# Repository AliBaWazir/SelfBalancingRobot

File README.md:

# README #

This README would normally document whatever steps are necessary to get your application up and running.

### What is this repository for? ###

This is Team Foxtrot's Repo for Self-Balancing Robot (SBR)

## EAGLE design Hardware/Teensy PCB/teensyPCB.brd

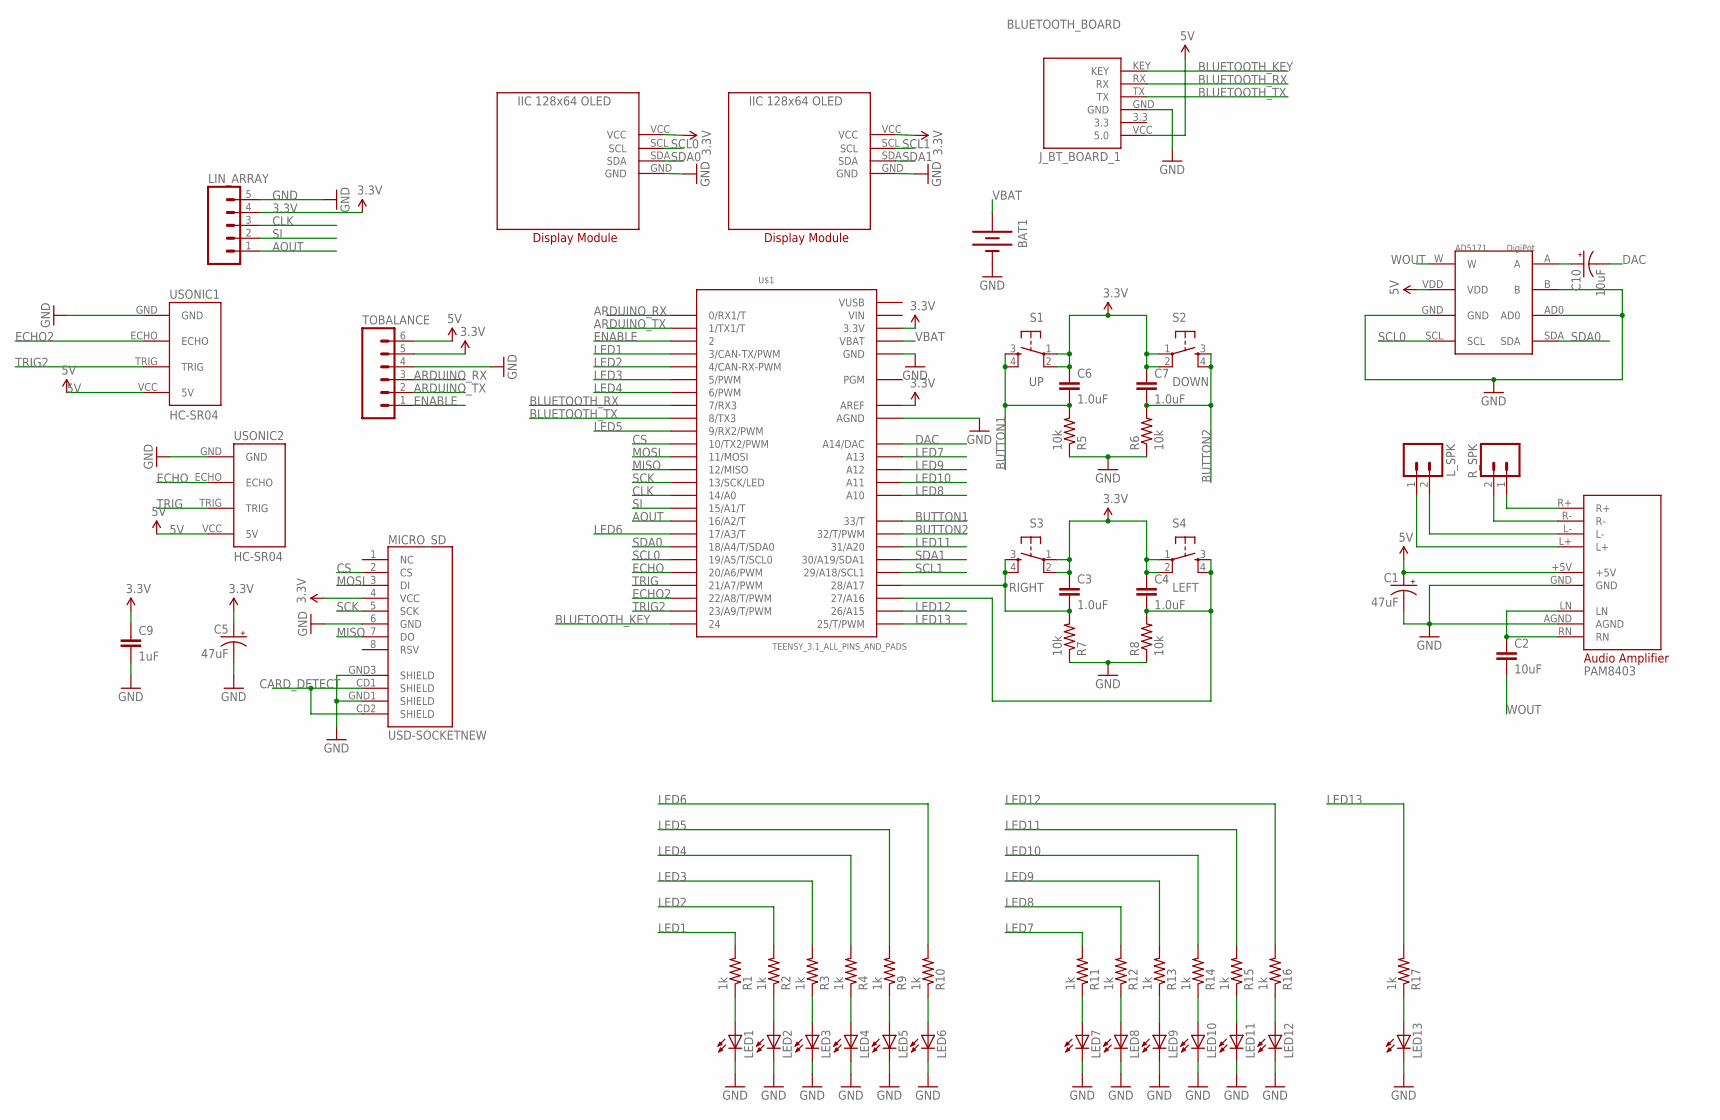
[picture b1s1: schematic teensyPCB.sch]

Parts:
BAT1: BATTERY20PTH; BATTCOM_20MM_PTH
C1, C5: 47uF; EIA3528
C2: 10uF; 0805
C3, C4, C6, C7: 1.0uF; 0805
C9: 1uF; 0805
C10: 10uF; EIA3528
J_BT_BOARD_1: BLUETOOTH_BOARD; BT_BOARD_FOOTPRINT
LED1, LED2, LED3, LED4, LED5, LED6, LED7, LED8, LED9, LED10, LED11, LED12, LED13: LEDCHIP-LED0805; CHIP-LED0805
LIN_ARRAY: M05LOCK; 1X05_LOCK
L_SPK: M02PTH; 1X02
MICRO_SD: USD-SOCKETNEW; MICRO-SD-SOCKET-PP
R1, R2, R3, R4, R9, R10, R11, R12, R13, R14, R15, R16, R17: 1k; 0805
R5, R6, R7, R8: 10k; 0805
R_SPK: M02PTH; 1X02
S1: UP; TACTILE-SWITCH-SMD
S2: DOWN; TACTILE-SWITCH-SMD
S3: RIGHT; TACTILE-SWITCH-SMD
S4: LEFT; TACTILE-SWITCH-SMD
TOBALANCE: M06POLAR_LOCK; MOLEX-1X6_LOCK
U$1: TEENSY_3.1_ALL_PINS_AND_PADS; TEENSY3_ALL_PINS_&_PADS
U$2, U$3: IIC128X64OLED
U$4: AUDIOAMPEBAY_VERSION; AUDIOAMP
U$5: DIGIPOT; SOT23-8L
USONIC1, USONIC2: HC-SR04; HC-SR04_FOOTPRINT

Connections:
3.3V: C3.1, C4.1, C5.A (+), C6.1, C7.1, C9.1, LIN_ARRAY.4, MICRO_SD.4 (VCC), S1.1, S1.2, S2.1, S2.2, S3.1, S3.2, S4.1, S4.2, TOBALANCE.5, U$1.3.3V, U$1.3.3V1 (3.3V), U$1.3.3V2 (3.3V), U$1.AREF, U$2.VCC, U$3.VCC
5V: C1.A (+), J_BT_BOARD_1.VCC (5.0), TOBALANCE.6, U$4.+5V, U$5.VDD, USONIC1.VCC (5V), USONIC2.VCC (5V)
AOUT: LIN_ARRAY.1, U$1.16/A2 (16/A2/T)
ARDUINO_RX: TOBALANCE.3, U$1.0 (0/RX1/T)
ARDUINO_TX: TOBALANCE.2, U$1.1 (1/TX1/T)
BLUETOOTH_KEY: J_BT_BOARD_1.KEY, U$1.24
BLUETOOTH_RX: J_BT_BOARD_1.RX, U$1.7 (7/RX3)
BLUETOOTH_TX: J_BT_BOARD_1.TX, U$1.8 (8/TX3)
BUTTON1: C6.2, R5.2, S1.3, S1.4, U$1.33 (33/T)
BUTTON2: C7.2, R6.2, S2.3, S2.4, U$1.32 (32/T/PWM)
BUTTON3: C3.2, R7.2, S3.3, S3.4, U$1.28 (28/A17)
BUTTON4: C4.2, R8.2, S4.3, S4.4, U$1.27 (27/A16)
CARD_DETECT: MICRO_SD.CD1 (SHIELD), MICRO_SD.CD2 (SHIELD)
CLK: LIN_ARRAY.3, U$1.14/A0
CS: MICRO_SD.2 (CS), U$1.10 (10/TX2/PWM)
DAC: C10.C (-), U$1.RESET/DAC (A14/DAC)
ECHO: U$1.20/A6 (20/A6/PWM), USONIC2.ECHO
ECHO2: U$1.22/A8 (22/A8/T/PWM), USONIC1.ECHO
ENABLE: TOBALANCE.1, U$1.2
GND: BAT1.2 (-), C1.C (-), C5.C (-), C9.2, J_BT_BOARD_1.GND, LED1.C, LED2.C, LED3.C, LED4.C, LED5.C, LED6.C, LED7.C, LED8.C, LED9.C, LED10.C, LED11.C, LED12.C, LED13.C, LIN_ARRAY.5, MICRO_SD.6 (GND), MICRO_SD.GND1 (SHIELD), MICRO_SD.GND3 (SHIELD), R5.1, R6.1, R7.1, R8.1, TOBALANCE.4, U$1.AGND, U$1.GND, U$1.GND1 (GND), U$1.GND2 (GND), U$2.GND, U$3.GND, U$4.AGND, U$4.GND, U$5.AD0, U$5.B, U$5.GND, USONIC1.GND, USONIC2.GND
LED1: R1.2, U$1.3 (3/CAN-TX/PWM)
LED2: R2.2, U$1.4 (4/CAN-RX-PWM)
LED3: R3.2, U$1.5 (5/PWM)
LED4: R4.2, U$1.6 (6/PWM)
LED5: R9.2, U$1.9 (9/RX2/PWM)
LED6: R10.2, U$1.17/A3 (17/A3/T)
LED7: R11.2, U$1.A13
LED8: R12.2, U$1.A10
LED9: R13.2, U$1.A12
LED10: R14.2, U$1.A11
LED11: R15.2, U$1.31 (31/A20)
LED12: R16.2, U$1.26 (26/A15)
LED13: R17.2, U$1.25 (25/T/PWM)
MISO: MICRO_SD.7 (DO), U$1.12 (12/MISO)
MOSI: MICRO_SD.3 (DI), U$1.11 (11/MOSI)
unnamed: C2.1, U$4.LN, U$4.RN
unnamed: C10.A (+), U$5.A
unnamed: R_SPK.1, U$4.R+
unnamed: R_SPK.2, U$4.R-
unnamed: L_SPK.2, U$4.L-
unnamed: L_SPK.1, U$4.L+
unnamed: LED1.A, R1.1
unnamed: LED2.A, R2.1
unnamed: LED3.A, R3.1
unnamed: LED4.A, R4.1
unnamed: LED5.A, R9.1
unnamed: LED6.A, R10.1
unnamed: LED7.A, R11.1
unnamed: LED8.A, R12.1
unnamed: LED9.A, R13.1
unnamed: LED10.A, R14.1
unnamed: LED11.A, R15.1
unnamed: LED12.A, R16.1
unnamed: LED13.A, R17.1
SCK: MICRO_SD.5 (SCK), U$1.13 (13/SCK/LED)
SCL0: U$1.19/A5 (19/A5/T/SCL0), U$2.SCL, U$5.SCL
SCL1: U$1.29 (29/A18/SCL1), U$3.SCL
SDA0: U$1.18/A4 (18/A4/T/SDA0), U$2.SDA, U$5.SDA
SDA1: U$1.30 (30/A19/SDA1), U$3.SDA
SI: LIN_ARRAY.2, U$1.15/A1 (15/A1/T)
TRIG: U$1.21/A7 (21/A7/PWM), USONIC2.TRIG
TRIG2: U$1.23/A9 (23/A9/T/PWM), USONIC1.TRIG
VBAT: BAT1.1 (+), U$1.VBAT
VIN: U$1.VIN
VUSB: U$1.VUSB
WOUT: C2.2, U$5.W

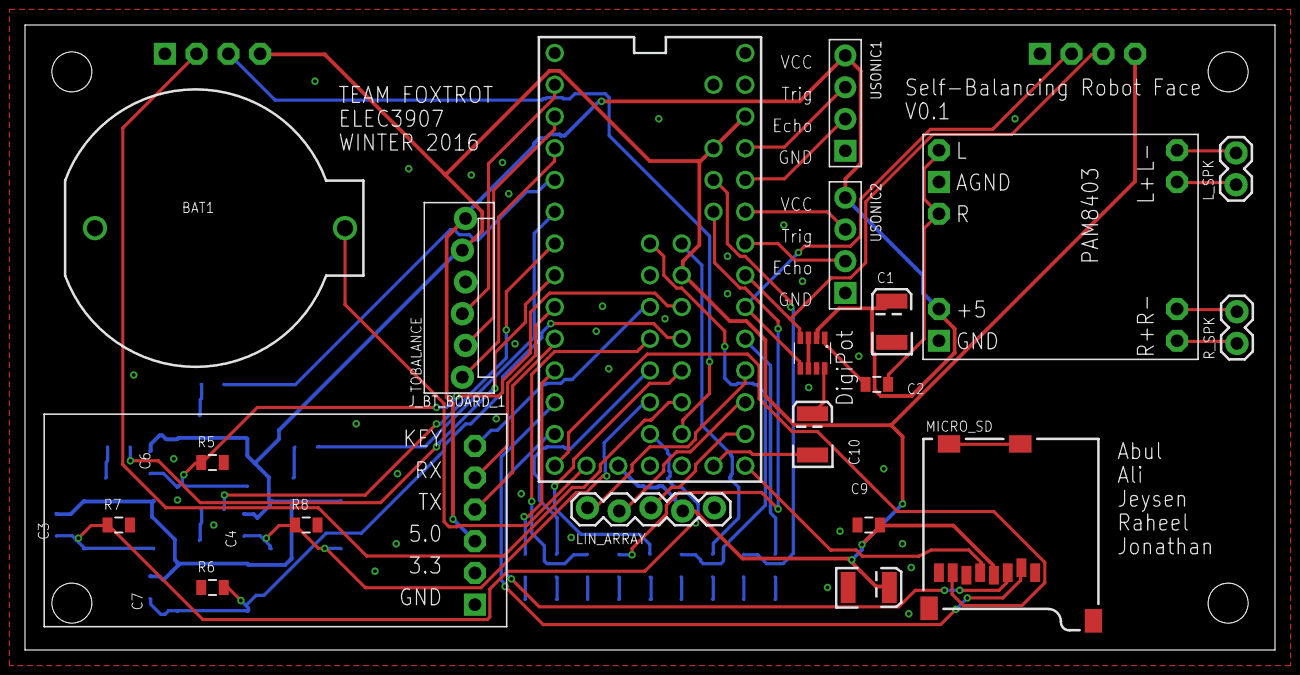
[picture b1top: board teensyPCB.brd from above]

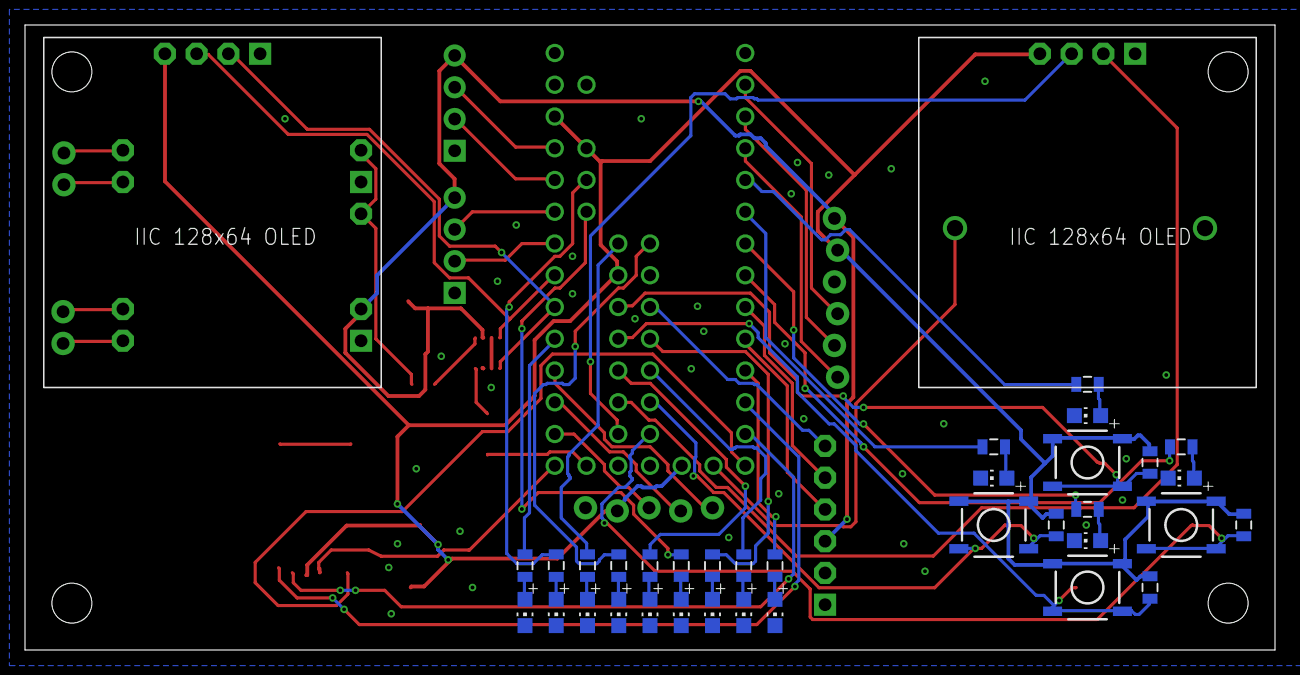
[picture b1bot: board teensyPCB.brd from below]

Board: 2 copper layers, 100.0 x 50.0 mm, 57 parts (36 on the bottom side), 64 nets.

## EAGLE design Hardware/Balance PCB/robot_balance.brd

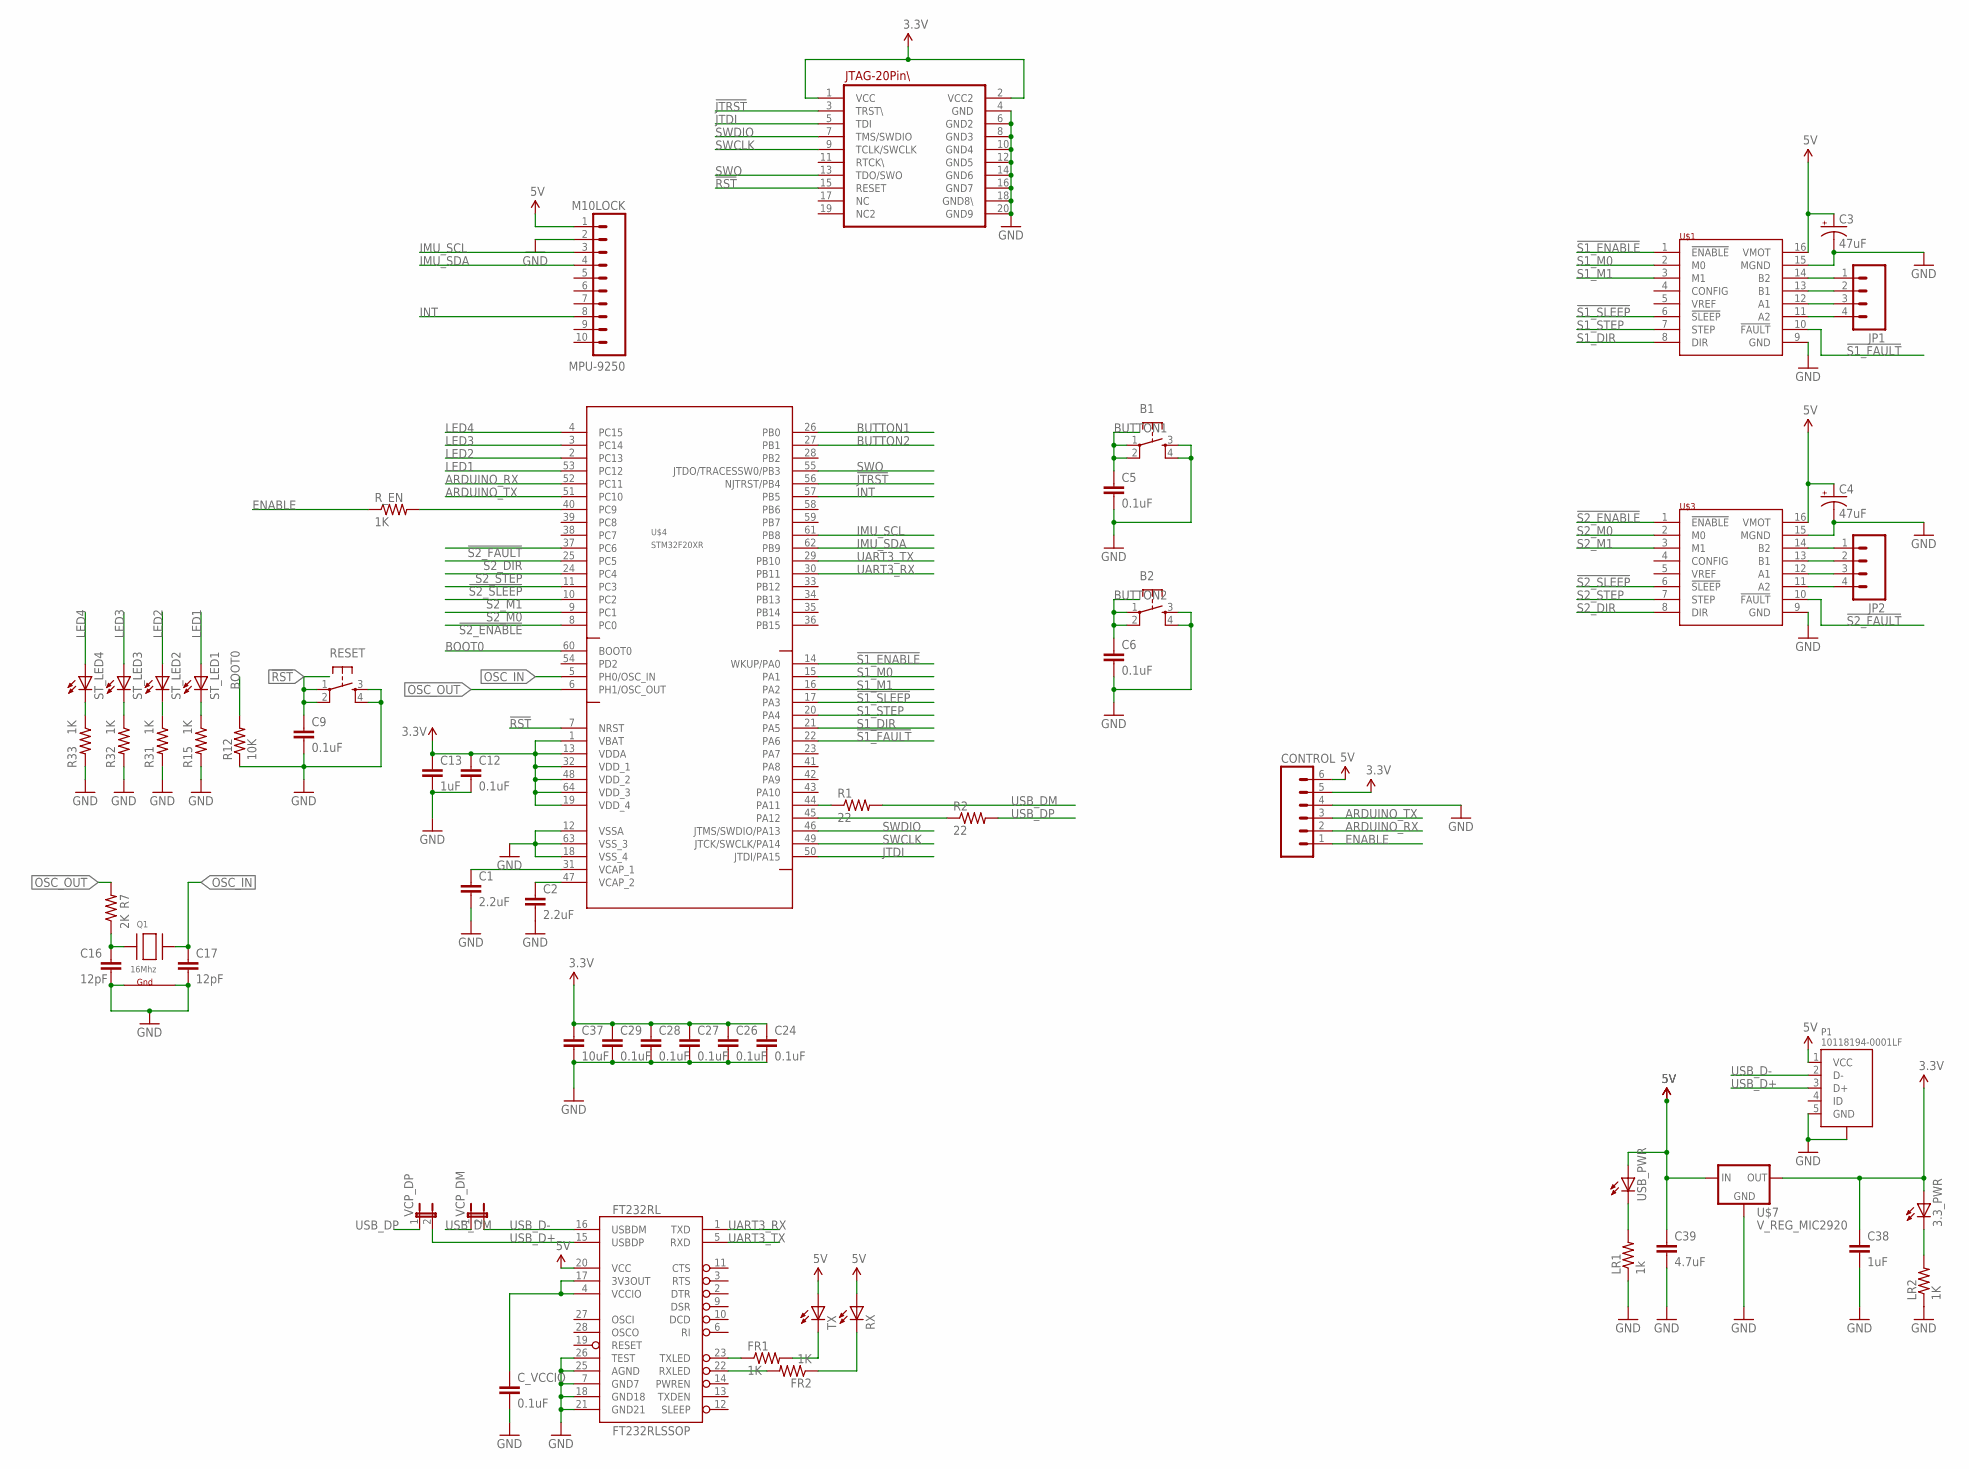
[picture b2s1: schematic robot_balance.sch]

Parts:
3.3_PWR: LEDCHIPLED_0805; CHIPLED_0805
B1, B2: TAC_SWITCHSMD; TACTILE-SWITCH-SMD
C1, C2: 2.2uF; 0805
C3, C4: 47uF; EIA3528
C5, C6, C9, C12, C24, C26, C27, C28, C29: 0.1uF; 0805
C13, C38: 1uF; 0805
C16, C17: 12pF; 0805
C37: 10uF; 0805
C39: 4.7uF; 0805
CONTROL: M06POLAR_LOCK; MOLEX-1X6_LOCK
C_VCCIO: 0.1uF; 0603-CAP
FR1, FR2: 1K; 0603-RES
FT232RL: FT232RLSSOP; SSOP28DB
JP1, JP2: M04POLAR_LOCK; MOLEX-1X4_LOCK
LR1: 1k; 0805
LR2: 1K; 0805
MPU-9250: M10LOCK; 1X10_LOCK
P1: 10118194-0001LF
Q1: 16Mhz; NX3225
R1, R2: 22; 0805
R7: 2K; 0805
R12: 10K; 0805
R15, R31, R32, R33: 1K; 0805
RESET: TAC_SWITCHSMD; TACTILE-SWITCH-SMD
RX: LEDCHIPLED_0805; CHIPLED_0805
R_EN: 1K; 0603-RES
ST_LED1, ST_LED2, ST_LED3, ST_LED4: LEDCHIPLED_0805; CHIPLED_0805
TX: LEDCHIPLED_0805; CHIPLED_0805
U$1, U$3: POLOLU_DRV8834
U$2: JTAG_20PIN; 2X10
U$4: STM32F20XR; LQFP64
U$7: V_REG_MIC2920; SOT223
USB_PWR: LEDCHIP-LED0805; CHIP-LED0805
VCP_DM: JUMPER-2SMD-NO; SJ_2S-NO
VCP_DP: JUMPER-2SMD-NO; SJ_2S-NO

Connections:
3.3V: 3.3_PWR.A, C12.1, C13.1, C24.1, C26.1, C27.1, C28.1, C29.1, C37.1, C38.1, CONTROL.5, U$2.1 (VCC), U$2.2 (VCC2), U$4.1 (VBAT), U$4.13 (VDDA), U$4.19 (VDD_4), U$4.32 (VDD_1), U$4.48 (VDD_2), U$4.64 (VDD_3), U$7.3 (OUT)
5V: C3.A (+), C4.A (+), C39.1, CONTROL.6, FT232RL.20 (VCC), MPU-9250.1, P1.1 (VCC), RX.A, TX.A, U$1.16 (VMOT), U$3.16 (VMOT), U$7.1 (IN), USB_PWR.A
!JTRST: U$2.3 (TRST\), U$4.56 (NJTRST/PB4)
!RST: C9.1, RESET.1, RESET.2, U$2.15 (RESET), U$4.7 (NRST)
!S1_ENABLE: U$1.1 (!ENABLE), U$4.14 (WKUP/PA0)
!S1_FAULT: U$1.10 (!FAULT), U$4.22 (PA6)
!S1_SLEEP: U$1.6 (!SLEEP), U$4.17 (PA3)
!S2_ENABLE: U$3.1 (!ENABLE), U$4.8 (PC0)
!S2_FAULT: U$3.10 (!FAULT), U$4.37 (PC6)
!S2_SLEEP: U$3.6 (!SLEEP), U$4.11 (PC3)
ARDUINO_RX: CONTROL.2, U$4.52 (PC11)
ARDUINO_TX: CONTROL.3, U$4.51 (PC10)
BOOT0: R12.2, U$4.60 (BOOT0)
BUTTON1: B1.1, B1.2, C5.1, U$4.26 (PB0)
BUTTON2: B2.1, B2.2, C6.1, U$4.27 (PB1)
ENABLE: CONTROL.1, R_EN.1
GND: B1.3, B1.4, B2.3, B2.4, C1.2, C2.2, C3.C (-), C4.C (-), C5.2, C6.2, C9.2, C12.2, C13.2, C16.2, C17.2, C24.2, C26.2, C27.2, C28.2, C29.2, C37.2, C38.2, C39.2, CONTROL.4, C_VCCIO.2, FT232RL.7 (GND7), FT232RL.18 (GND18), FT232RL.21 (GND21), FT232RL.25 (AGND), FT232RL.26 (TEST), LR1.1, LR2.1, MPU-9250.2, P1.5 (GND), P1.M1 (SHIELD), P1.M2 (SHIELD), P1.M3 (SHIELD), P1.M4 (SHIELD), Q1.2 (G2), Q1.4 (G1), R12.1, R15.2, R31.2, R32.2, R33.2, RESET.3, RESET.4, U$1.9 (GND), U$1.15 (MGND), U$2.4 (GND), U$2.6 (GND2), U$2.8 (GND3), U$2.10 (GND4), U$2.12 (GND5), U$2.14 (GND6), U$2.16 (GND7), U$2.18 (GND8\), U$2.20 (GND9), U$3.9 (GND), U$3.15 (MGND), U$4.12 (VSSA), U$4.18 (VSS_4), U$4.63 (VSS_3), U$7.2 (GND)
IMU_SCL: MPU-9250.3, U$4.61 (PB8)
IMU_SDA: MPU-9250.4, U$4.62 (PB9)
INT: MPU-9250.8, U$4.57 (PB5)
JTDI: U$2.5 (TDI), U$4.50 (JTDI/PA15)
LED1: ST_LED1.A, U$4.53 (PC12)
LED2: ST_LED2.A, U$4.2 (PC13)
LED3: ST_LED3.A, U$4.3 (PC14)
LED4: ST_LED4.A, U$4.4 (PC15)
unnamed: JP1.1, U$1.14 (B2)
unnamed: C1.1, U$4.31 (VCAP_1)
unnamed: JP1.2, U$1.13 (B1)
unnamed: JP1.3, U$1.12 (A1)
unnamed: JP1.4, U$1.11 (A2)
unnamed: R_EN.2, U$4.40 (PC9)
unnamed: R1.1, U$4.44 (PA11)
unnamed: FR1.1, FT232RL.23 (TXLED)
unnamed: FR1.2, TX.C
unnamed: FR2.2, FT232RL.22 (RXLED)
unnamed: FR2.1, RX.C
unnamed: C2.1, U$4.47 (VCAP_2)
unnamed: C_VCCIO.1, FT232RL.4 (VCCIO), FT232RL.17 (3V3OUT)
unnamed: R2.1, U$4.45 (PA12)
unnamed: 3.3_PWR.C, LR2.2
unnamed: LR1.2, USB_PWR.C
unnamed: JP2.1, U$3.14 (B2)
unnamed: JP2.2, U$3.13 (B1)
unnamed: JP2.3, U$3.12 (A1)
unnamed: JP2.4, U$3.11 (A2)
unnamed: R15.1, ST_LED1.C
unnamed: R31.1, ST_LED2.C
unnamed: R32.1, ST_LED3.C
unnamed: R33.1, ST_LED4.C
unnamed: C16.1, Q1.1 (X1), R7.1
OSC_IN: C17.1, Q1.3 (X2), U$4.5 (PH0/OSC_IN)
OSC_OUT: R7.2, U$4.6 (PH1/OSC_OUT)
S1_DIR: U$1.8 (DIR), U$4.21 (PA5)
S1_M0: U$1.2 (M0), U$4.15 (PA1)
S1_M1: U$1.3 (M1), U$4.16 (PA2)
S1_STEP: U$1.7 (STEP), U$4.20 (PA4)
S2_DIR: U$3.8 (DIR), U$4.25 (PC5)
S2_M0: U$3.2 (M0), U$4.9 (PC1)
S2_M1: U$3.3 (M1), U$4.10 (PC2)
S2_STEP: U$3.7 (STEP), U$4.24 (PC4)
SWCLK: U$2.9 (TCLK/SWCLK), U$4.49 (JTCK/SWCLK/PA14)
SWDIO: U$2.7 (TMS/SWDIO), U$4.46 (JTMS/SWDIO/PA13)
SWO: U$2.13 (TDO/SWO), U$4.55 (JTDO/TRACESSW0/PB3)
UART3_RX: FT232RL.1 (TXD), U$4.30 (PB11)
UART3_TX: FT232RL.5 (RXD), U$4.29 (PB10)
USB_D+: FT232RL.15 (USBDP), P1.3 (D+), VCP_DP.2
USB_D-: FT232RL.16 (USBDM), P1.2 (D-), VCP_DM.2
USB_DM: R1.2, VCP_DM.1
USB_DP: R2.2, VCP_DP.1

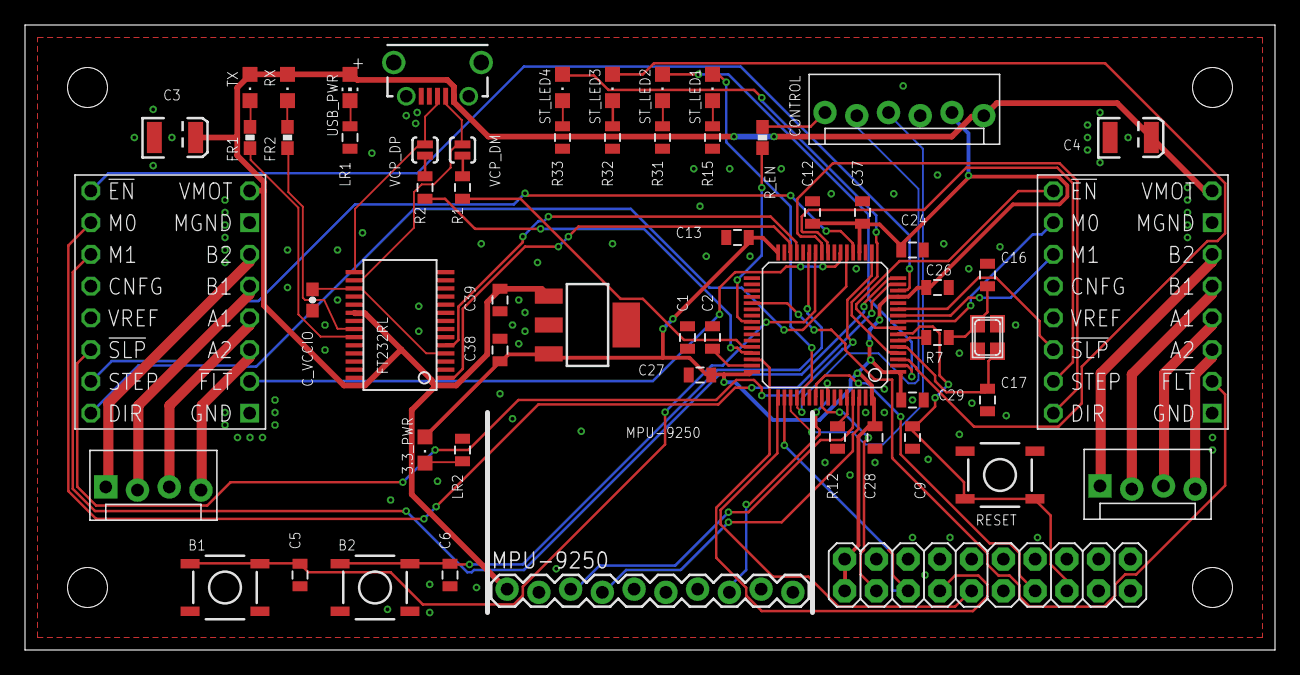
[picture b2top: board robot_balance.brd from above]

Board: 2 copper layers, 100.0 x 50.0 mm, 58 parts (0 on the bottom side), 69 nets.

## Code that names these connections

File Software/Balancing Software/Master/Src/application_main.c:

#include "application_main.h"
#include "tm_stm32_usart.h"
#include "buttons.h"
#include "arm_math.h"




#define MINANGLE 10000
float temps[2];


int32_t zeroAngle = 72;
uint8_t calibrateFlag = 0;
uint8_t state = 3;
uint32_t calibrateCounter = 200;
double acceleration = 0;
double newSpeed = 0;
double oldSpeed = -0.1;
double angleSetpoint = 0;
double ac1, ac2, ac3, ac4;
uint32_t counter = 0;

uint8_t ledCounter = 0;



void setup(){
    initLED();
    setupButtons();
    TM_DELAY_Init();
    initSteppers();
    initTimerInterrupt();
    setupLog();
    stepperEnable();
    init_pid();
}


void userLoop(){
    if(runFlag >= 1){
        runFlag = 0;
        //runSpeed(); 
        
    }
}

void noMatlab(int32_t angle){
    application_pid(angle);
}

void application_main(int32_t angle){
    updateButtons();    
    switch (state){
        case 0:
            stepperDisable();
            TM_GPIO_SetPinLow(LEDPORT, LEDALL);
        break;
        case 1:
            stepperEnable();
            switch(ledCounter){
                case 0:
                    TM_GPIO_TogglePinValue(LEDPORT, LED1);
                break;
                case 32:
                    TM_GPIO_TogglePinValue(LEDPORT, LED2);
                break;
                case 64:
                    TM_GPIO_TogglePinValue(LEDPORT, LED3);
                break;
                case 96:
                    TM_GPIO_TogglePinValue(LEDPORT, LED4);
                break;
                default:
                break;         
            }
            ledCounter +=16;
            parseCommands();
            noMatlab(angle);
            logNewLine();
        break;
        case 2:
            stepperDisable();
            calibrateZero(angle);
        break;
        case 3:
            if(HAL_GetTick()<10000)TM_GPIO_TogglePinValue(LEDPORT, LED3);
        break;
        default:
        break;                
    }
}
void setCalibrateFlag(uint8_t flag){
    calibrateFlag = flag;
}

TIM_HandleTypeDef TIM_Handle;
void initTimerInterrupt(void)
{
    __TIM4_CLK_ENABLE();
    TIM_Handle.Init.Prescaler = 0;
    TIM_Handle.Init.CounterMode = TIM_COUNTERMODE_UP;
    TIM_Handle.Init.Period = 8399; //50us//13439;
    TIM_Handle.Instance = TIM4;   //Same timer whose clocks we enabled
    HAL_TIM_Base_Init(&TIM_Handle);     // Init timer
    HAL_TIM_Base_Start_IT(&TIM_Handle); // start timer interrupts
    HAL_NVIC_SetPriority(TIM4_IRQn, 5, 15);
    HAL_NVIC_EnableIRQ(TIM4_IRQn);

}

void calibrateZero(int32_t angle){
    
    
    if(!calibrateCounter){
        calibrateCounter = 200;
        zeroAngle = angle;
        TM_GPIO_SetPinLow(LEDPORT, LED2);
        setState(1);
    }
    else{
        calibrateCounter--;
        TM_GPIO_TogglePinValue(LEDPORT, LED2);
    }
  
}
void setState(uint8_t newState){
    state = newState;
}
int32_t getZeroAngle(void){
    return zeroAngle;
}
void TIM4_IRQHandler(void)
{
    if (__HAL_TIM_GET_FLAG(&TIM_Handle, TIM_FLAG_UPDATE) != RESET)      //In case other interrupts are also running
    {
        if (__HAL_TIM_GET_ITSTATUS(&TIM_Handle, TIM_IT_UPDATE) != RESET)
        {
            __HAL_TIM_CLEAR_FLAG(&TIM_Handle, TIM_FLAG_UPDATE);
            /*put your code here */
            
            stepperRun();
            
            
        }
    }
}

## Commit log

2016-01-11 Created file from example. Blahblah
2016-01-11 Changed time to 2000 ms
2016-01-12 Replaced 144 pin Balancing MCU with smaller 64 pin version and added a .gitignore file
2016-01-12 Added FTDI USB to Serial Converter as ALI suggested
2016-01-12 Put a larger JTAG connector
2016-01-14 First Commit of Teensy PCB
2016-01-14 added some parts
2016-01-14 added library files
2016-01-14 Micro usb instead of Mini
2016-01-14 reserving audio pins
2016-01-14 changed inter-board connect to 6 pin and added enable line
2016-01-15 example sketches
2016-01-15 Jeysen's commit
2016-01-15 Jeysen connected SD card in eagle schematic
2016-01-16 final commit today
2016-01-16 Latest version of Tilen's libraries
2016-01-16 MPU-9250 output working and 5.1.3 python demo code working on STM32F4-Discovery
2016-01-16 Tried to find the proper quaternion order without success
2016-01-16 Added Arduino prototype code for reference
2016-01-17 #ifdef example
2016-01-17 included math.h. Trying to calculate Tait–Bryan angle pitch from quaternions.
2016-01-17 angle working to some extent
2016-01-18 demo code
2016-01-18 Stepper motor clean slate project and arduino library to be ported
2016-01-18 Stepper library ported. Need to finish Arduino32.cpp and implement the remaining functions there.
2016-01-18 latest
2016-01-18 Added VCP solder jumpers
2016-01-18 Layout changed slightly and labels placed
2016-01-18 Updated DRV8834 footprint
2016-01-18 Moved MPU to middle of board
2016-01-18 Fixed gitignore
2016-01-18 layout
2016-01-18 route
2016-01-19 matlab initial code
2016-01-20 Added Arduino examples and library for the light sensor
2016-01-20 matlab
2016-01-20 gitignore
2016-01-20 no message
2016-01-20 Arduino pinMode function ported
2016-01-21 digitalWrite and pinMode working
2016-01-21 Lots of progress: Stepper driver functional
2016-01-22 steppers
2016-01-22 Stepper setup
2016-01-24 Blank slate new project
2016-01-24 Created an eagle footprint for the OLED module - Jeysen
2016-01-24 Balance files
2016-01-24 Updated OLED module library and added modules to teensy PCB
2016-01-24 audio amp eagle footprint
2016-01-24 Added audio amp to pcb
2016-01-25 First attempt at wiring the audio (could be totally wrong)
2016-01-25 Modified audio connections
2016-01-26 Board layout
2016-01-27 Merged stepper and MPU projects
2016-01-27 README.md edited online with Bitbucket
2016-01-27 Added a debug function for the single frame buffer of Array Sensor code and saved the date in a single frame array.
2016-01-27 GPIO HAL working
2016-01-27 flashing led
2016-01-27 project files
2016-01-27 Steppers acceleration code
2016-01-29 Work on stepper motor driver and matlab
2016-01-29 Modified audio component
2016-01-29 progress- fiddling with timer
2016-01-30 Added wiring of the Linear Array sensor to the teency chip
2016-01-30 Added the wiring for the ultrasonic sensor to the Teency chip
2016-01-30 cat.ino
2016-02-01 PID implementation
2016-02-01 Modified audio amplifier dimensions and pin spacing
2016-02-01 Updated OLED dimensions/pin spacing
2016-02-02 Abdul's changes. He did not save the .brd file so it will need to be regenerated
2016-02-03 Bug fixes: USB Virtual COM port Gyro not starting up properly sometimes Switched gyro I2C port to I2C3
    At this point IMU is still resetting sometimes and is drifting for unknown reason, but it starts up reliably.
2016-02-03 Developed the code to detect the positions of black lines and count of them
2016-02-03 pcb update
2016-02-03 Added maxim library
2016-02-03 Switched output to acce
2016-02-03 Created library component for digipot
2016-02-06 Wired digipot, added push buttons with voltage debounce, updated audio amplifier
2016-02-06 fixed error
2016-02-08 Worked on board schematic, added coin cell slot
2016-02-10 Did some modification to the Linear Array Sensor code
2016-02-10 Created the master file for the Teensy based code
2016-02-11 Added "state" push buttons
2016-02-16 improvements to stabilize
2016-02-19 Did some coding in the linear sensor array driver and organized the Teensy master file
2016-02-22 Updated hole spacing and layout
2016-02-22 layout work
2016-02-22 Did some coding for the line following. Added functions to control the motors directitons
2016-02-22 more layout
2016-02-22 UART working
2016-02-22 fixed HC-05 text and added leds
2016-02-24 Added digipot and LED code to Teensy Main Software folder
2016-02-29 balancing updATES
2016-03-01 Begin transition to new PCB
2016-03-02 Added timer interrupt for stepping and small fixes
2016-03-02 fixed 5V connected to buttons
2016-03-04 Added code for interrupt buttons
2016-03-05 Changed button pins after @Jeysen found an error
2016-03-05 Supplemental
2016-03-05 Integrated the Teensy code
2016-03-06 Did some development in the code integration
2016-03-06 Did some enhancements to the Teensy master
2016-03-07 Maybe need this
2016-03-07 Update gitignore
2016-03-07 Buttons and LED to turn motors on and off, angle corrected to new mounting position, ready to tune balancing
2016-03-09 Fixed bug with Vcap
2016-03-10 Big improvements to stabiize
2016-03-11 PCB finalized
2016-03-20 teensyPCB gerbers
2016-03-20 Revert "teensyPCB gerbers"
    This reverts commit f1b49bbba4c0790f8e04c0b1d8f1af333fc37c44.
2016-03-20 THIS THING IS DRIVING MY CRAZY! Trying a different approach.
2016-03-23 Balance Improvements
2016-03-23 Updates in order to attempt merge
2016-03-23 Enhanced the Ultrasonic Driver code
2016-03-27 Changes robot mode variable name
2016-03-27 Created Bluetooth module driver. manual mode is now controlling the robot motion given data from top the Bluetooth driver.
2016-03-27 Created a speaker driver
2016-03-27 Created hex array for a robot eye, added code to master file (display_driver), created code to move eye left and right (located in the ssd1306_128x64... file)
2016-03-28 linear_sensor_array driver now considers a black line if and only if its two edge point pairs are detected
2016-03-28 Changed parameter values for linear_sensor_array_driver
2016-03-28 Added a new function to the display_driver to display an object in a specific display. Defined the locations within the code of line following mode where a sound has to be played or an object has to 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
2016-03-28 Fixed a compilation error.
2016-03-30 Line following mode now is able to follow two black lines besides the single black line.
2016-03-30 bringing up to date
2016-03-30 Created a driver for the LEDs. Created a function to control the mouth LEDs.
2016-03-30 Integrated the LED talking function with the line following mode.
2016-03-31 Coded a function in the motor driver to pass a struct of control data for the motor from Teensy to ARM processor.
2016-03-31 Added the software communication protocol between Teensy and ARM processor
2016-04-01 Put the linear_senor_array_deiver in testing mode. Added a function call to turn on 9 LEDs. Enhanced the motor driver code.
2016-04-02 LED driver now integrated with the motor driver to indicate the moving direction. Motor driver now prints the packet data for debugging purposes. Line following mode commands the robot forward if the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
2016-04-02 Changes to rebase
2016-04-02 implemented USB serial
2016-04-03 Added pictures
2016-04-03 Balancing cleanup
2016-04-03 Removed the i2c_t3 modified library. Had the Teensy-ARM communication working. Did some code clean up.
2016-04-03 Added a function to display objects on a specific display or both
2016-04-03 Added a header and src files to handle events. Added the possible events and their handler functions.
2016-04-03 Hex data and bmp/gif files for left and right blinking eyes
2016-04-03 Integrated eye data into display_driver.cpp, added modified graphics libraries
2016-04-03 Balancing quite well at this point
2016-04-04 Standing #2
2016-04-04 Added state machine for buttons
2016-04-04 Modified push button code, added digipot code
2016-04-04 Different sound effects, WAV 16-bit PCM 44100Hz
2016-04-04 High D balancing
2016-04-04 D balancing with a bit of flutter
2016-04-04 playing with sensor params - balancing well
2016-04-04 Happy with stabilization at this point
2016-04-04 Balancing update. Demo ready and reliable
2016-04-05 Updated WAV file names, created a table for event/response, added image data
2016-04-05 Fixed images
2016-04-05 Updated display and sound player code
2016-04-05 Display and Audio stuff
2016-04-06 Two animated eyes are working in manual mode. Front ultrasonic working with manual mode and with OLEDs too. Bluetooth is now working by giving F, B, L, R signals.
2017-08-08 Committing last changes before the demo. Added Arduino modified libraries to the repository.

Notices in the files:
parts and their libraries:
SparkFun-Electromechanical: Licensing: Creative Commons ShareAlike 4.0 International - https://creativecommons.org/licenses/by-sa/4.0
SparkFun-Resistors: Licensing: CC v3.0 Share-Alike You are welcome to use this library for commercial purposes.
